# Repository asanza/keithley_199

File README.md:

# Keithley 199 Digital Board Replacement

This is an upgrade replacement for the digital control board on Keithley 199 multimeters.

The [Keithley 199](doc/k199_op_maint.pdf) is a digital multimeter built in the nineties. It is capable of current, voltage and resistance measurements and also provides a gpib interface for remote control.

These multimeters contains three electronic circuit boards, one which contains the analog circuitry, including analog signal conditioning and analog digital converter, a display board which contains the user interface, and a digital control board, with a processor who controls display, gpib interface and analog digital converter.

This repository contains hardware and software files needed to build a replacement of the digital control board.

# Features
- Voltage Measurement 0.3, 3, 30, 300 VDC/VAC 6.5 digits
- Current Measurement 30mA, 3A DC/AC,  6.5 digits
- Resistance Measurement 300-3GOhm, 6.5 digits, 4 wire.
- Arbitrary integration period
- SCPI interface
- Free Software

# Building the hardware 

The hardware files are in [Kicad](http://kicad-pcb.org/) format. Gerber files are (not yet) available.

# Building the software

The software was built with the [Microchip Toolchain](http://www.microchip.com/mplab/compilers). 

We use [Ceedling](http://www.throwtheswitch.org/ceedling/) for building and testing (but for comfort, [MPLABX](http://www.microchip.com/mplab/mplab-x-ide) files are available). 

In order to build the software, go to the root directory and do:

```
$rake release

```
Or to perform the unit tests:
```
$rake test:all
```

## Hardware

The hardware is pretty basic. It contains a pic32mx controller which do the heavy lifting. An ftdi chip provides an usb interface, while two open drain drivers controll the led displays. The external trigger input and output are connected to the microcontroller through the necessary input/output protection.

## Calibration

TODO

## Principles of Operation

The interesting part is the Control of the analog board. The analog board contains a series of switches that are controlled with a shift register. The adc conversion is performed with a discrete charge-balance adc which returns a pulse train with a pulse count proportional to the input voltage. The control of the adc is performed by the microcontroller in the digital board and should observe a precise timing in order to guarantee adc accuracy.

As shown in the figure above, the charge balance phase starts after the controller sends a start of conversion to the analog board. While the charge balance phase takes place, the controller counts the number of pulses it receives from the analog board. The analog board only send pulses on the up parts, thus the number of pulses is proportional to the charge acumulated. After exactly 16.66 msecs the controller sends an stop of conversion and the single slope phase starts, discharging the integrator. While discharge takes place, the controller counts the number of pulses received.

# Licence

```
 * Copyright (c) 2015, Diego F. Asanza. All rights reserved.
 *
 * This software is free software; you can redistribute it and/or
 * modify it under the terms of the GNU Lesser General Public
 * License as published by the Free Software Foundation; either
 * version 2.1 of the License, or (at your option) any later version.
 *
 * This library is distributed in the hope that it will be useful,
 * but WITHOUT ANY WARRANTY; without even the implied warranty of
 * MERCHANTABILITY or FITNESS FOR A PARTICULAR PURPOSE.  See the GNU
 * Lesser General Public License for more details.
 *
 * You should have received a copy of the GNU Lesser General Public
 * License along with this library; if not, write to the Free Software
 * Foundation, Inc., 51 Franklin Street, Fifth Floor, Boston,
 * MA 02110-1301  USA
 *
 ```

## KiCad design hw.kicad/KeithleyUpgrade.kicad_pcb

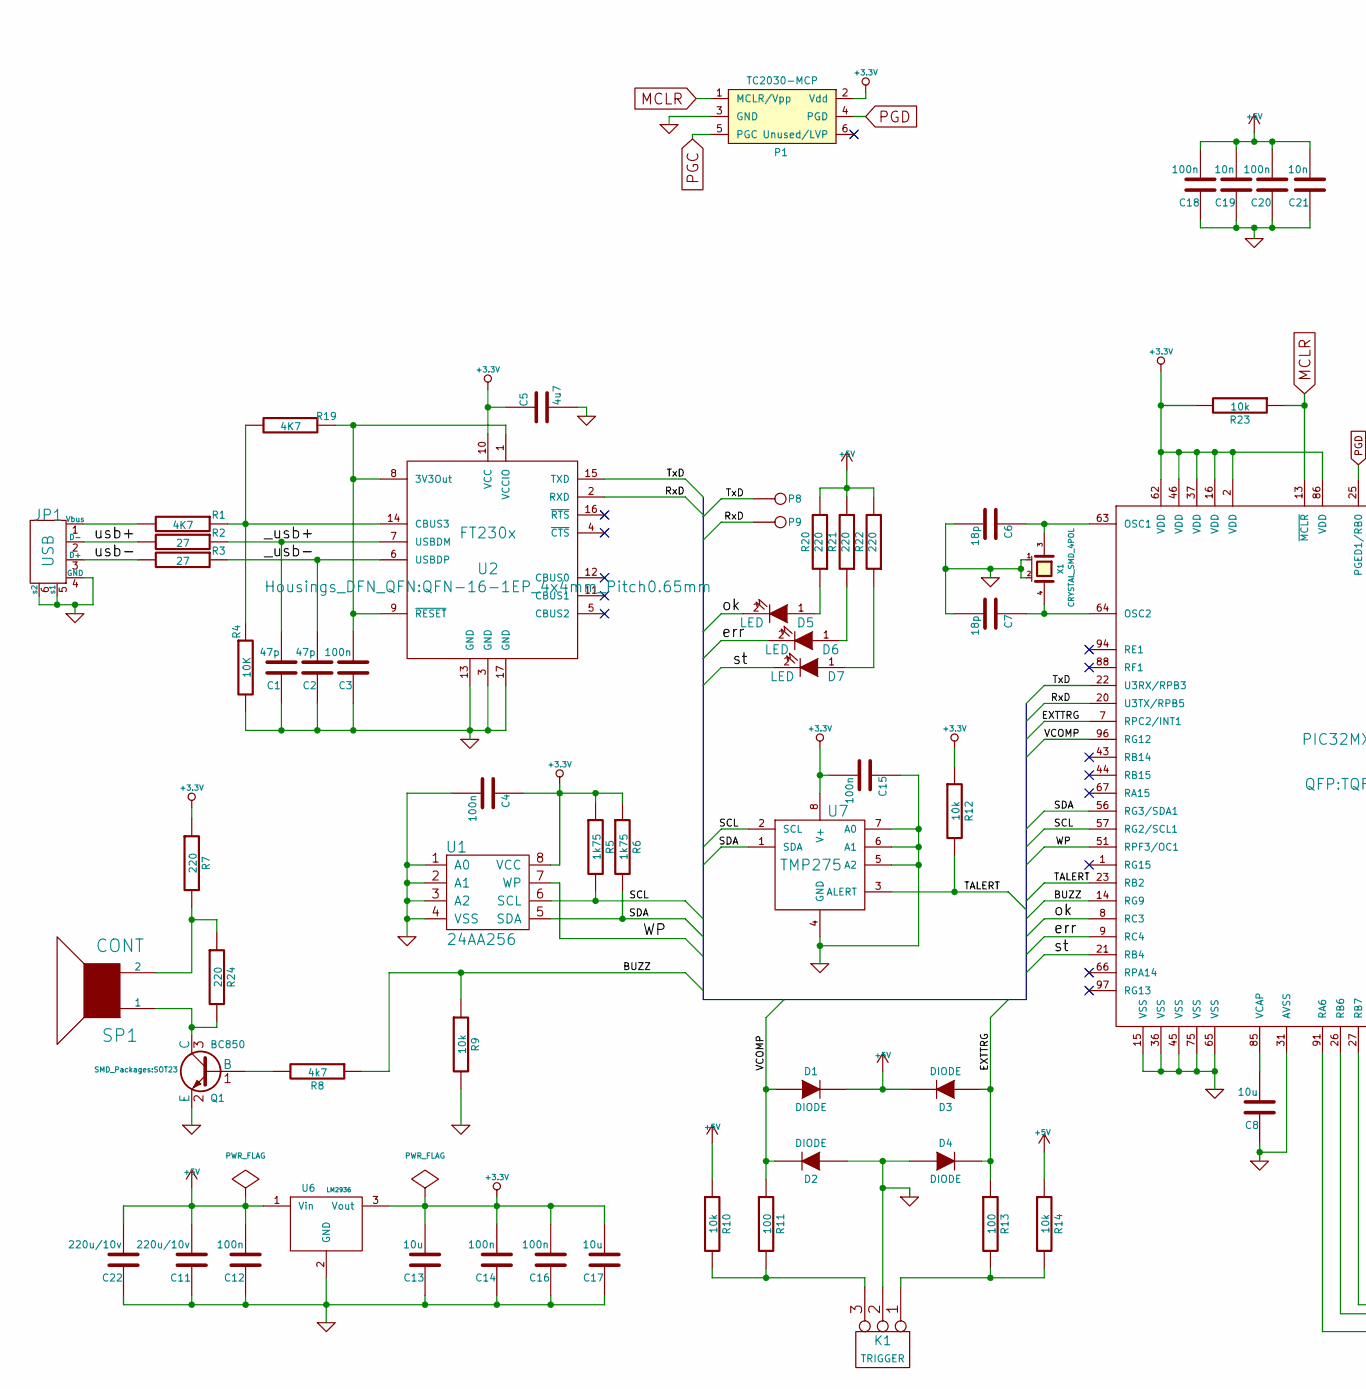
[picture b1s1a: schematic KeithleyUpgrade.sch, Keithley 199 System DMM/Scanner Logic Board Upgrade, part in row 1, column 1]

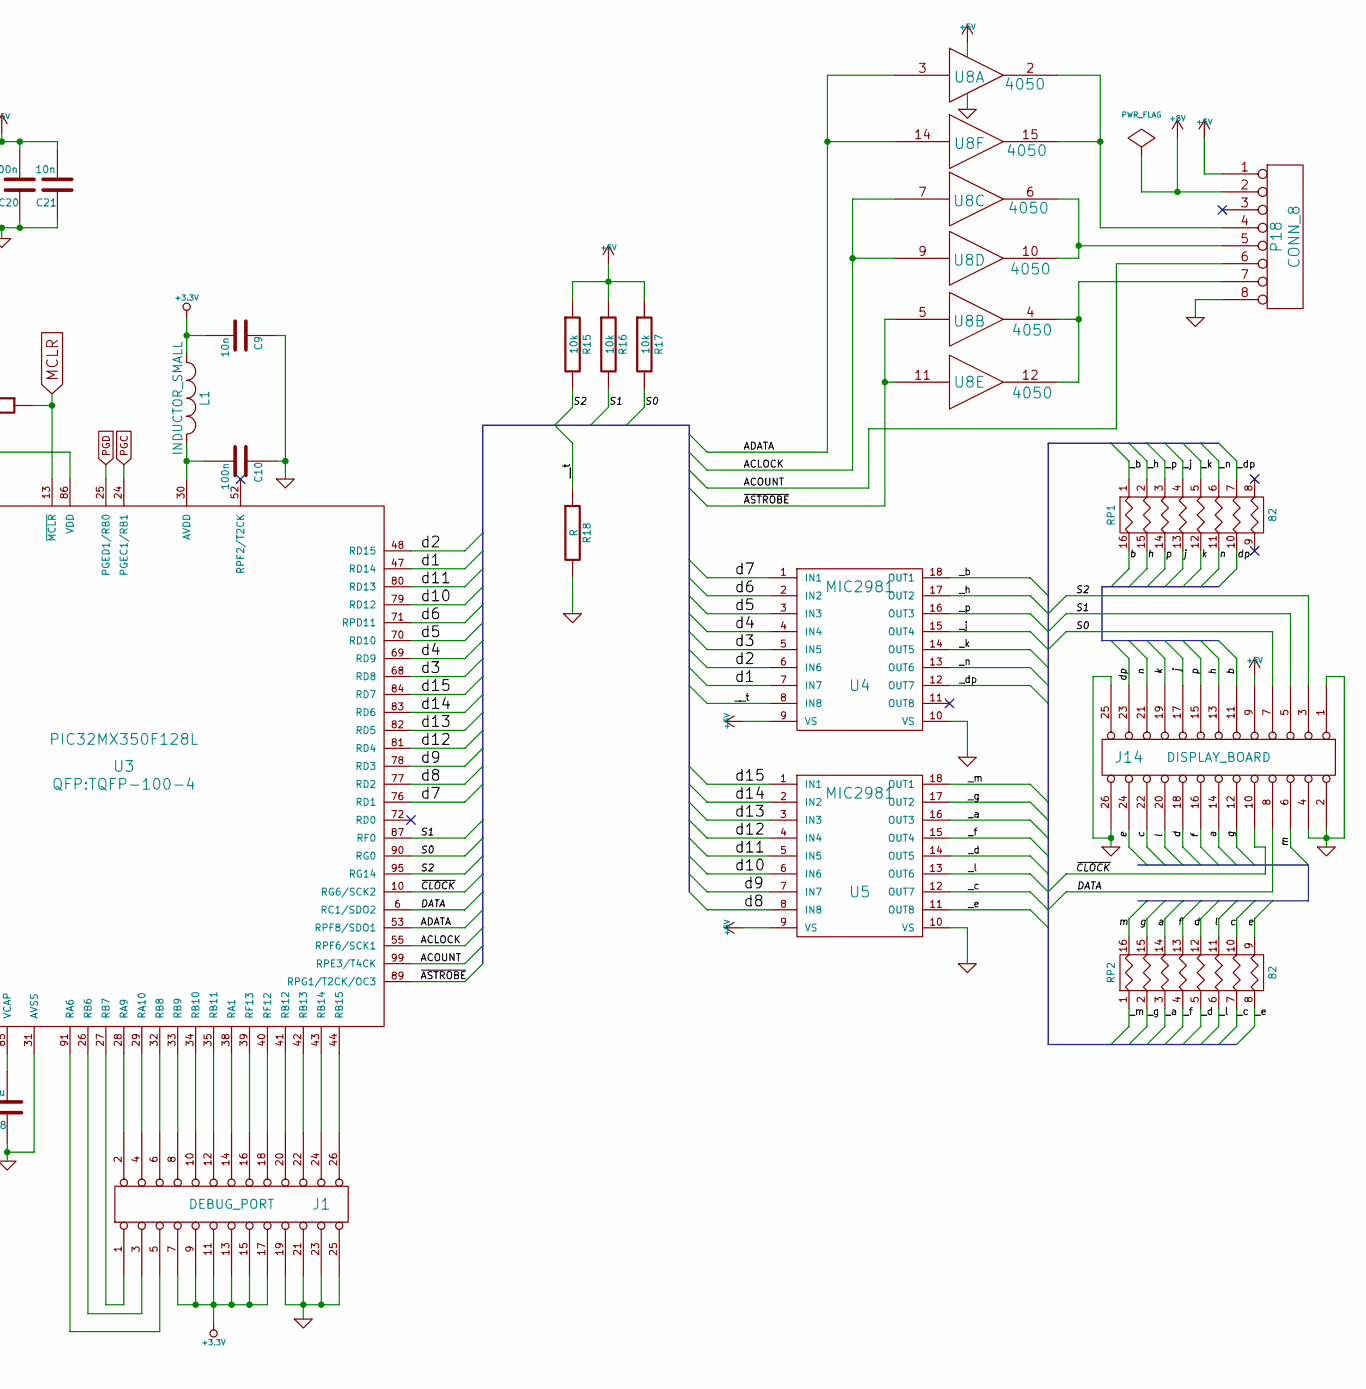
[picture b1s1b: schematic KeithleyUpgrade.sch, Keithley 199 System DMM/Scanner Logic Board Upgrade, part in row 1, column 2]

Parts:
C1, C2: 47p; C_0805
C3, C4, C10, C12, C14, C15, C16, C18, C20: 100n; C_0805
C5: 4u7; C_1206
C6, C7: 18p; C_0805
C8: 10u; C_0805
C9, C19, C21: 10n; C_0805
C11, C22: 220u/10v; c_elec_10x10
C13, C17: 10u; C_1210
D1, D2, D3, D4: DIODE; Diode-SMA_Standard
D5, D6, D7: LED; LED-0805
J1: DEBUG_PORT; header_straight_2x13
J14: DISPLAY_BOARD; header_straight_2x13
JP1: USB; USB_B
K1: TRIGGER; bornier3
L1: INDUCTOR_SMALL; SMD-1210
P1: TC2030-MCP; TC2030-NL_SMALL
P8, P9: TP1; SIL-1
P18: CONN_8; Pin_Header_Straight_1x08
Q1: BC850; SOT23
R1: 4K7; SM0805
R2, R3: 27; SM0805
R4: 10K; SM0805
R5, R6: 1k75; SM0805
R7: 220; SM0805
R8: 4k7; SM0805
R9, R10, R12, R14, R15, R16, R17, R23: 10k; R_0805
R11, R13: 100; R_0805
R18: R; R_0805
R19: 4K7; R_0805
R20, R21, R22, R24: 220; R_0805
RP1, RP2: 82; SOM16
SP1: CONT; Elko_vert_DM14_RM5
U1: 24AA256; SOIC-8_N
U2: FT230x; QFN-16-1EP_4x4mm_Pitch0.65mm
U3: PIC32MX350F128L; TQFP-100-4
U4, U5: MIC2981; soic-18
U6: LM2936; DPAK2
U7: TMP275; SOIC-8_N
U8: 4050; SOIC-16_Narrow
X1: CRYSTAL_SMD_4POL; XTAL_SMD_5x3_2

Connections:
/ACLOCK: U3.55 (RPF6/SCK1), U8.7, U8.9
/ACOUNT: P18.6, U3.99 (RPE3/T4CK)
/ADATA: U3.53 (RPF8/SDO1), U8.3, U8.14
/BUZZ: R8.1, R9.1, U3.14 (RG9)
/DATA: J14.8, U3.6 (RC1/SDO2)
/EXTTRG: D3.1 (A), D4.2 (K), R13.1, U3.7 (RPC2/INT1)
/RxD: P9.1, U2.2 (RXD), U3.20 (U3TX/RPB5)
/S0: J14.7, R17.2, U3.90 (RG0)
/S1: J14.5, R16.2, U3.87 (RF0)
/S2: J14.3, R15.2, U3.95 (RG14)
/SCL: R5.2, U1.6 (SCL), U3.57 (RG2/SCL1), U7.2 (SCL)
/SDA: R6.2, U1.5 (SDA), U3.56 (RG3/SDA1), U7.1 (SDA)
/TALERT: R12.2, U3.23 (RB2), U7.3 (ALERT)
/TxD: P8.1, U2.15 (TXD), U3.22 (U3RX/RPB3)
/VCOMP: D1.1 (A), D2.2 (K), R11.1, U3.96 (RG12)
/WP: U1.7 (WP), U3.51 (RPF3/OC1)
/__t: R18.1, U4.8 (IN8)
/_a: RP2.3, U5.16 (OUT3)
/_b: RP1.1, U4.18 (OUT1)
/_c: RP2.7, U5.12 (OUT7)
/_d: RP2.5, U5.14 (OUT5)
/_dp: RP1.7, U4.12 (OUT7)
/_e: RP2.8, U5.11 (OUT8)
/_f: RP2.4, U5.15 (OUT4)
/_g: RP2.2, U5.17 (OUT2)
/_h: RP1.2, U4.17 (OUT2)
/_j: RP1.4, U4.15 (OUT4)
/_k: RP1.5, U4.14 (OUT5)
/_l: RP2.6, U5.13 (OUT6)
/_m: RP2.1, U5.18 (OUT1)
/_n: RP1.6, U4.13 (OUT6)
/_p: RP1.3, U4.16 (OUT3)
/_usb+: C1.2, R2.1, U2.7 (USBDM)
/_usb-: C2.2, R3.1, U2.6 (USBDP)
/a: J14.14, RP2.14 (R3)
/b: J14.11, RP1.16 (R1)
/c: J14.22, RP2.10 (R7)
/d: J14.18, RP2.12 (R5)
/d1: U3.47 (RD14), U4.7 (IN7)
/d2: U3.48 (RD15), U4.6 (IN6)
/d3: U3.68 (RD8), U4.5 (IN5)
/d4: U3.69 (RD9), U4.4 (IN4)
/d5: U3.70 (RD10), U4.3 (IN3)
/d6: U3.71 (RPD11), U4.2 (IN2)
/d7: U3.76 (RD1), U4.1 (IN1)
/d8: U3.77 (RD2), U5.8 (IN8)
/d9: U3.78 (RD3), U5.7 (IN7)
/d10: U3.79 (RD12), U5.6 (IN6)
/d11: U3.80 (RD13), U5.5 (IN5)
/d12: U3.81 (RD4), U5.4 (IN4)
/d13: U3.82 (RD5), U5.3 (IN3)
/d14: U3.83 (RD6), U5.2 (IN2)
/d15: U3.84 (RD7), U5.1 (IN1)
/dp: J14.23, RP1.10 (R7)
/e: J14.24 (P20), RP2.9 (R8)
/err: D6.2 (K), U3.9 (RC4)
/f: J14.16, RP2.13 (R4)
/g: J14.12, RP2.15 (R2)
/h: J14.13, RP1.15 (R2)
/j: J14.17, RP1.13 (R4)
/k: J14.19, RP1.12 (R5)
/l: J14.20, RP2.11 (R6)
/m: J14.6, RP2.16 (R1)
/n: J14.21, RP1.11 (R6)
/ok: D5.2 (K), U3.8 (RC3)
/p: J14.15, RP1.14 (R3)
/st: D7.2 (K), U3.21 (RB4)
/usb+: JP1.2 (D-), R2.2
/usb-: JP1.3 (D+), R3.2
/~ASTROBE: U3.89 (RPG1/T2CK/OC3), U8.5, U8.11
/~CLOCK: J14.10, U3.10 (RG6/SCK2)
GND: C1.1, C2.1, C3.1, C4.2, C5.2, C6.2, C7.2, C8.1, C9.1, C10.1, C11.1, C12.1, C13.1, C14.1, C15.1, C16.1, C17.1, C18.1, C19.1, C20.1, C21.1, C22.1, D2.1 (A), D4.1 (A), J1.19, J1.21, J1.23, J1.25 (P24), J14.1, J14.2, J14.4, J14.25 (P24), J14.26 (P22), JP1.4 (GND), JP1.5 (s1), JP1.6 (s2), K1.2 (PM), P1.3 (GND), P18.8, Q1.2 (E), R4.2, R9.2, R18.2, U1.1 (A0), U1.2 (A1), U1.3 (A2), U1.4 (VSS), U2.3 (GND), U2.13 (GND), U2.17 (GND), U3.15 (VSS), U3.31 (AVSS), U3.36 (VSS), U3.45 (VSS), U3.65 (VSS), U3.75 (VSS), U4.10 (VS), U5.10 (VS), U6.2 (GND), U7.4 (GND), U7.5 (A2), U7.6 (A1), U7.7 (A0), U8.8 (VSS), X1.1 (case), X1.2 (case)
MCLR: P1.1 (MCLR/Vpp), R23.1, U3.13 (~MCLR)
unnamed: C3.2, R19.1, U2.1 (VCCIO), U2.8 (3V3Out), U2.9 (~RESET)
unnamed: C6.1, U3.63 (OSC1), X1.3
unnamed: C7.1, U3.64 (OSC2), X1.4
unnamed: C8.2, U3.85 (VCAP)
unnamed: C10.2, L1.2, U3.30 (AVDD)
unnamed: D5.1 (A), R20.1
unnamed: D6.1 (A), R21.1
unnamed: D7.1 (A), R22.1
unnamed: J1.1, U3.27 (RB7)
unnamed: J1.2, U3.28 (RA9)
unnamed: J1.3, U3.26 (RB6)
unnamed: J1.4, U3.29 (RA10)
unnamed: J1.5, U3.91 (RA6)
unnamed: J1.6, U3.32 (RB8)
unnamed: J1.8, U3.33 (RB9)
unnamed: J1.10, U3.34 (RB10)
unnamed: J1.12, U3.35 (RB11)
unnamed: J1.14, U3.38 (RA1)
unnamed: J1.16, U3.39 (RF13)
unnamed: J1.18, U3.40 (RF12)
unnamed: J1.20, U3.41 (RB12)
unnamed: J1.22, U3.42 (RB13)
unnamed: JP1.1 (Vbus), R1.2
unnamed: K1.1, R13.2, R14.2
unnamed: K1.3, R10.2, R11.2
unnamed: P18.4, U8.2, U8.15
unnamed: P18.5, U8.6, U8.10
unnamed: P18.7, U8.4, U8.12
unnamed: Q1.1 (B), R8.2
unnamed: Q1.3 (C), R24.2, SP1.1
unnamed: R1.1, R4.1, R19.2, U2.14 (CBUS3)
unnamed: R7.2, R24.1, SP1.2
PGC: P1.5 (PGC), U3.24 (PGEC1/RB1)
PGD: P1.4 (PGD), U3.25 (PGED1/RB0)

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
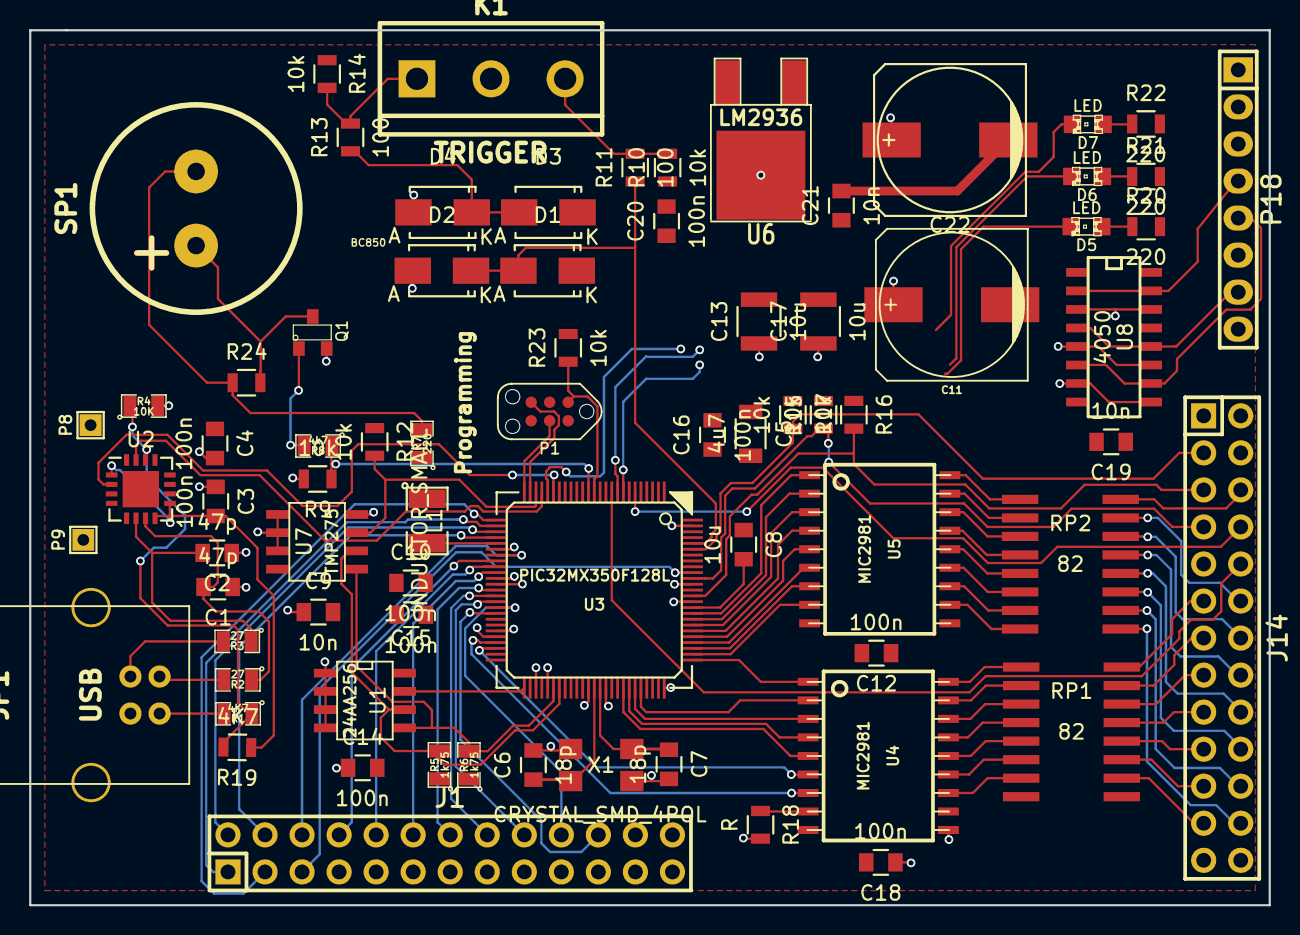
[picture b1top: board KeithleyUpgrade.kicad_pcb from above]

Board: 4 copper layers, 85.0 x 60.0 mm, 75 parts (0 on the bottom side), 109 nets.

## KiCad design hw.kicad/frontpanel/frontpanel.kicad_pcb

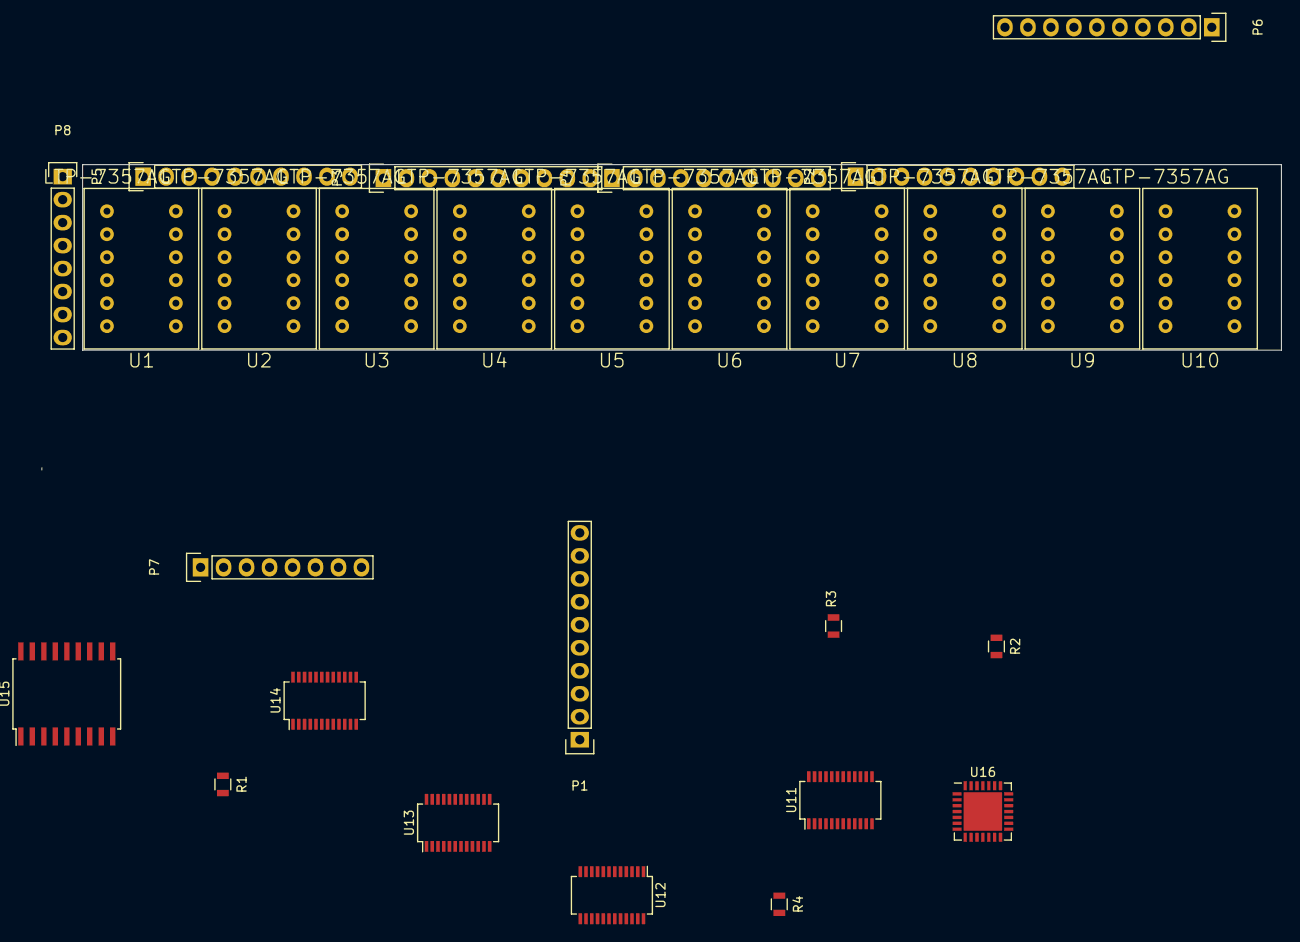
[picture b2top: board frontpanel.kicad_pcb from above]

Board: 2 copper layers, 28 parts (0 on the bottom side), 19 nets, no tracks yet.

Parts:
P1, P2, P3, P4, P5, P6: CONN_10; Pin_Header_Straight_1x10
P7, P8: CONN_8; Pin_Header_Straight_1x08
R1, R2, R3, R4: R; R_0805
U1, U2, U3, U4, U5, U6, U7, U8, U9, U10: LTP-7357AG
U11, U12, U13, U14: TLC5928; SSOP-24_3.9x8.7mm_Pitch0.635mm
U15: MIC2981; SOIC-18_7.5x11.6mm_Pitch1.27mm
U16: DSPIC33FJ64GP802; QFN-28-1EP_6x6mm_Pitch0.65mm

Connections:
/ROW1: U1.12, U2.12, U3.12, U4.12, U5.12, U6.12, U7.12, U8.12, U9.12, U10.12
/ROW2: U1.11, U2.11, U3.11, U4.11, U5.11, U6.11, U7.11, U8.11, U9.11, U10.11
/ROW3: U1.2, U2.2, U3.2, U4.2, U5.2, U6.2, U7.2, U8.2, U9.2, U10.2
/ROW4: U1.9, U2.9, U3.9, U4.9, U5.9, U6.9, U7.9, U8.9, U9.9, U10.9
/ROW5: U1.4, U2.4, U3.4, U4.4, U5.4, U6.4, U7.4, U8.4, U9.4, U10.4
/ROW6: U1.5, U2.5, U3.5, U4.5, U5.5, U6.5, U7.5, U8.5, U9.5, U10.5
/ROW7: U1.6, U2.6, U3.6, U4.6, U5.6, U6.6, U7.6, U8.6, U9.6, U10.6
GND: R1.2, R2.2, R3.2, R4.2, U11.1, U12.1, U13.1, U14.1, U15.10
unnamed: R1.1, U14.23
unnamed: R2.1, U11.23
unnamed: R3.1, U12.23
unnamed: R4.1, U13.23
unnamed: U11.2, U12.22
unnamed: U11.3, U12.3, U13.3, U14.2
unnamed: U11.4, U12.4, U13.4, U14.3
unnamed: U11.21, U12.21, U13.21, U14.4
unnamed: U12.2, U13.22
unnamed: U13.2, U14.22
VCC: U11.24, U12.24, U13.24, U14.24, U15.9

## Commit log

2014-09-18 new interface to adc, now send hardcoded sequences directly
2014-09-18 voltage AC and DC working
2014-09-19 mA seems to work, but need more testing
2014-09-19 amperes ac measurement working
2014-09-19 adding the multiplexer sequences
2014-09-19 update display refresh frequency, it was way too bright
2014-09-22 adding libscpi submodule
2014-09-22 moving measurement task to its own file
2014-09-26 Adding files wrongly left out on last commit
2014-09-29 Delete spec.odt
    delete empty file
2014-09-29 Delete KeithleyUpgrade.pdf
    delete empty file
2014-10-03 refactoring the adc interface
2014-10-03 refactoring adc interface
2014-10-04 ac measurement moved to adcseq.c
2014-10-04 added some documentation
2014-10-04 pressing the volt button two times does not cause changes between ac and dc modes anymore.
2014-12-25 adding tdd files
2014-12-25 remove pic18 files
2014-12-25 adding git ignores
2014-12-25 adding missing folders
2014-12-25 wait for simulator to finish
2014-12-26 hal_uart_open implemented
2014-12-26 added ringbuffer files
2014-12-27 added ringbuffer to uart
2014-12-28 simplify ringbuff interface
2014-12-28 fixing unit tests
2015-01-16 fixing broken tests
2015-01-16 refactoring USB_UART name
2015-01-16 using os for uart send and receive functions
2015-01-17 adding missing files
2015-01-17 uart module new implemented
2015-01-19 implementing i2c
2015-01-19 i2c basics working
2015-01-19 updating eeprom interface
2015-01-19 eeprom abstraction added
2015-01-22 fixed cristal footprint
2015-01-23 added some files
2015-01-23 added driver for temp sensor
2015-01-23 fix: revert broken commit
2015-01-23 refactor: moving timer to hal
2015-01-23 refactor: moving hardware dependences to hal
2015-01-23 working on modularization
2015-01-24 refactor: change key names
2015-01-24 refactor: moving formatting functions
2015-01-24 chore: update scpi-parser
2015-01-24 chore: adding libscpi to config files
2015-01-25 refactor adc interface
2015-01-25 add state representation
2015-01-25 refactoring some interfaces
2015-01-27 chore: cleaning up
2015-05-26 update uart module
2015-05-30 fixing uart issues
2015-05-30 add missing files
2015-05-30 playing with usb_uart
2015-05-30 enabled usb_uart
2015-06-01 adding repoversion info
2015-06-04 Refactoring system interface
2015-07-14 fixing format
2015-07-14 adding dmm task'
2015-07-14 fix: core timer interrupt is not being updated
2015-07-14 fix: keyboard now return key event if key was pressed.
2015-07-14 fix: update keyboard repetition frequency
2015-07-14 ugly keyboard code
2015-07-14 fix display brightness
2015-07-15 simplify key events
2015-07-15 adding firmware information at startup
2015-07-15 added symbol '=' to chartable
2015-07-15 only print git hash into version string for better display
2015-07-15 added default settings function
2015-07-15 added functions to store settings
2015-07-15 reload last settings on startup. Show frequency on startup
2015-07-15 added symbol '*' to chartable
2015-07-16 refactor: change interface for hal_adc, now period is entered in us, to be full hardware independent
2015-07-16 refactoring settings and calibration values
    #
    #
2015-07-16 refactor: simplify interface
2015-07-16 get an unique id for each supported hardware configuration. Useful to save and restore calibration values, as there is one calibration value for each hardware configuration
2015-07-16 fix: eeprom bug
2015-07-17 refactor: change adcseq to adc_control_sequence
2015-07-17 fix: fix eeprom read nack. feat: return KEY_NONE when key released.
2015-07-17 defined system interface
2015-07-18 refactor settings interface
2015-07-18 adding task skeletons
2015-07-18 fixing settings
2015-07-18 fix: set settings
2015-07-18 updating configuration
2015-07-18 refactor settings interface*
2015-07-18 feat: implement task skeletons
2015-07-19 feat: implement range up/down skeleton
2015-07-19 refactor: systask to systasks
2015-07-19 documentation fixed.
2015-07-19 fix: range up and down
2015-07-21 added forgotten file
2015-07-21 fix error printing double
2015-08-23 refactor system interface
2015-08-23 adding task management code. Signed-off-by:Diego F. Asanza <f.asanza@gmail.com>
2015-08-23 task switching seems to work
2015-08-24 quick and dirty task switching
2015-08-24 highlighting digits now working
2015-08-25 removing unused files
2015-08-25 fix: bad scan key due to buggy highlight digit code Signed-off-by:Diego F. Asanza <f.asanza@gmail.com>
2015-08-25 fix: keys correspond now to its numerical value. Signed-off-by:Diego F. Asanza <f.asanza@gmail.com>
2015-08-25 fix: evt clear not working due to false conditional. we wait until all data is received from queue. Signed-off-by:Diego F. Asanza <f.asanza@gmail.com>
2015-08-25 fix: single adc calls didnt work because strobe was being continuously sended. Signed-off-by:Diego F. Asanza <f.asanza@gmail.com>
2015-08-25 input calibration values working
2015-08-26 add scl and sda pin defines Signed-off-by:Diego F. Asanza <f.asanza@gmail.com>
2015-08-26 fix: wrong sequence existence comparisson. Signed-off-by:Diego F. Asanza <f.asanza@gmail.com>
2015-08-26 calibration code working
2015-08-26 working dc-voltage and dc-current. Working calibration code
2015-08-26 fix compiler warnings. Activate no-short-double option
2015-08-27 added double printing functions
2015-08-27 fix: manage sign correctly
2015-08-27 fix: substitute formating functions with custom functions. (xc32 printf for 64bit double are broken).
2015-08-27 fix calibration issues with long double
2015-08-27 fix calibration issues
2015-08-28 change wait for working. filter size is now 100 measurements. Signed-off-by:Diego F. Asanza <f.asanza@gmail.com>
2015-08-28 string conversion right rounding. Signed-off-by:Diego F. Asanza <f.asanza@gmail.com>
2015-08-28 implemented fixed width double to str Signed-off-by:Diego F. Asanza <f.asanza@gmail.com>
2015-08-28 remove diagnostic code
2015-08-28 working on ac measurements
2015-08-28 fix: double conversion bug
2015-08-28 fix double conversion bug
2015-08-28 add resolution change as settings
2015-08-29 adding 6.5 digits resolution mode
2015-08-29 implemented temperature measurement by internal sensor
2015-08-29 fixed temperature code
2015-08-29 implementing save settings
2015-08-29 fix bug hang when pressing the temperature button fast
2015-08-29 integrate scpi. implement idn command
2015-08-29 scpi integration
2015-08-29 removing unnecesary code
2015-08-30 replace dtoa with statically allocated version
2015-08-30 add dtostr for scpi library
2015-08-30 fix scpi print double
2015-08-30 fix broken tests
2015-08-30 lock settings to make it reentrant
2015-08-30 fixed autoranging issues
2015-08-30 fix memory allocation error
2015-08-30 fix buff overflow
2015-08-30 remove display add mode function
2015-08-30 fixed shift key behaviour
2015-08-30 fixed configuration.
2015-08-31 refactor some code
2015-08-31 more refactoring
2015-08-31 autorange working
2015-08-31 temperature does not autoranges
2015-08-31 save and restore configuration working
2015-08-31 refactoring
2015-09-01 Implemented correct rounding
2015-09-01 creating wlan task for wlan module
2015-09-02 fix rounding errors
2015-09-02 communication with wlan module works
2015-09-06 fix bug on double to string conversion.
2015-09-06 300Ohm resistance range seems to work. Noise on last digit.
2015-09-07 working Ohms and KOhms ranges
2015-09-07 300KOhms working
2015-09-07 settings now save actual input
2015-09-07 increase i2c frequency. Set default calibration values for temperature
2015-09-13 fix: calibration not being restored when using autorange
2015-09-13 updating schematic
2015-12-07 fix compilation issues
2015-12-07 fix compilation errors
2015-12-07 fix some errors
2015-12-07 cleaning up
2016-01-06 adding frontpanel hw
2016-01-06 adding fp files
2016-01-06 add jekyll skeleton
2016-01-06 update url
2016-01-07 update base url
2016-01-07 update post
2016-01-07 add new theme
2016-01-07 Create gh-pages branch via GitHub
2016-01-07 change index
2016-01-10 reworking task management
2016-01-10 fixing task key behaviour
2016-01-10 fix bad assert value
2016-01-11 fix: eeprom needs reset after changing i2c from temperature sensor to eeprom
2016-01-11 fix: null pointer when string does not contains decimal point
2016-01-16 fix: task suspend resume when changing settings
2016-01-16 fix: hangup after repeated volt settings selection
2016-01-16 fix: fix resistance measurement for 300k and 3M scales
2016-02-07 update files
2016-02-14 add images
2016-02-14 reverting changes
2016-02-19 add .gitlab-ci.yml file
2016-02-20 fix: fix floating point string rounding
2016-02-20 fix: add forgotten files
2016-03-06 add documentation
2016-03-06 change to mkdocs
2016-05-21 project.yml: create release configuration
2016-05-21 project.yml: fix version number on code.
2016-05-21 project.yml: fix set git version as define for availability in code.
2016-05-21 README.md: update documentation
2016-05-21 README.md: update documentation.
2016-05-21 update documentation
2016-05-21 added a couple of nets to the pcb
2016-05-22 addedd documentation@
2016-05-22 addedd documentation
2016-05-22 add some documentation
2016-06-28 replace start image
2016-06-28 update front picture
2016-07-07 fix configuration file.
2016-07-07 fix configuration file
2016-07-07 fix configuration files
